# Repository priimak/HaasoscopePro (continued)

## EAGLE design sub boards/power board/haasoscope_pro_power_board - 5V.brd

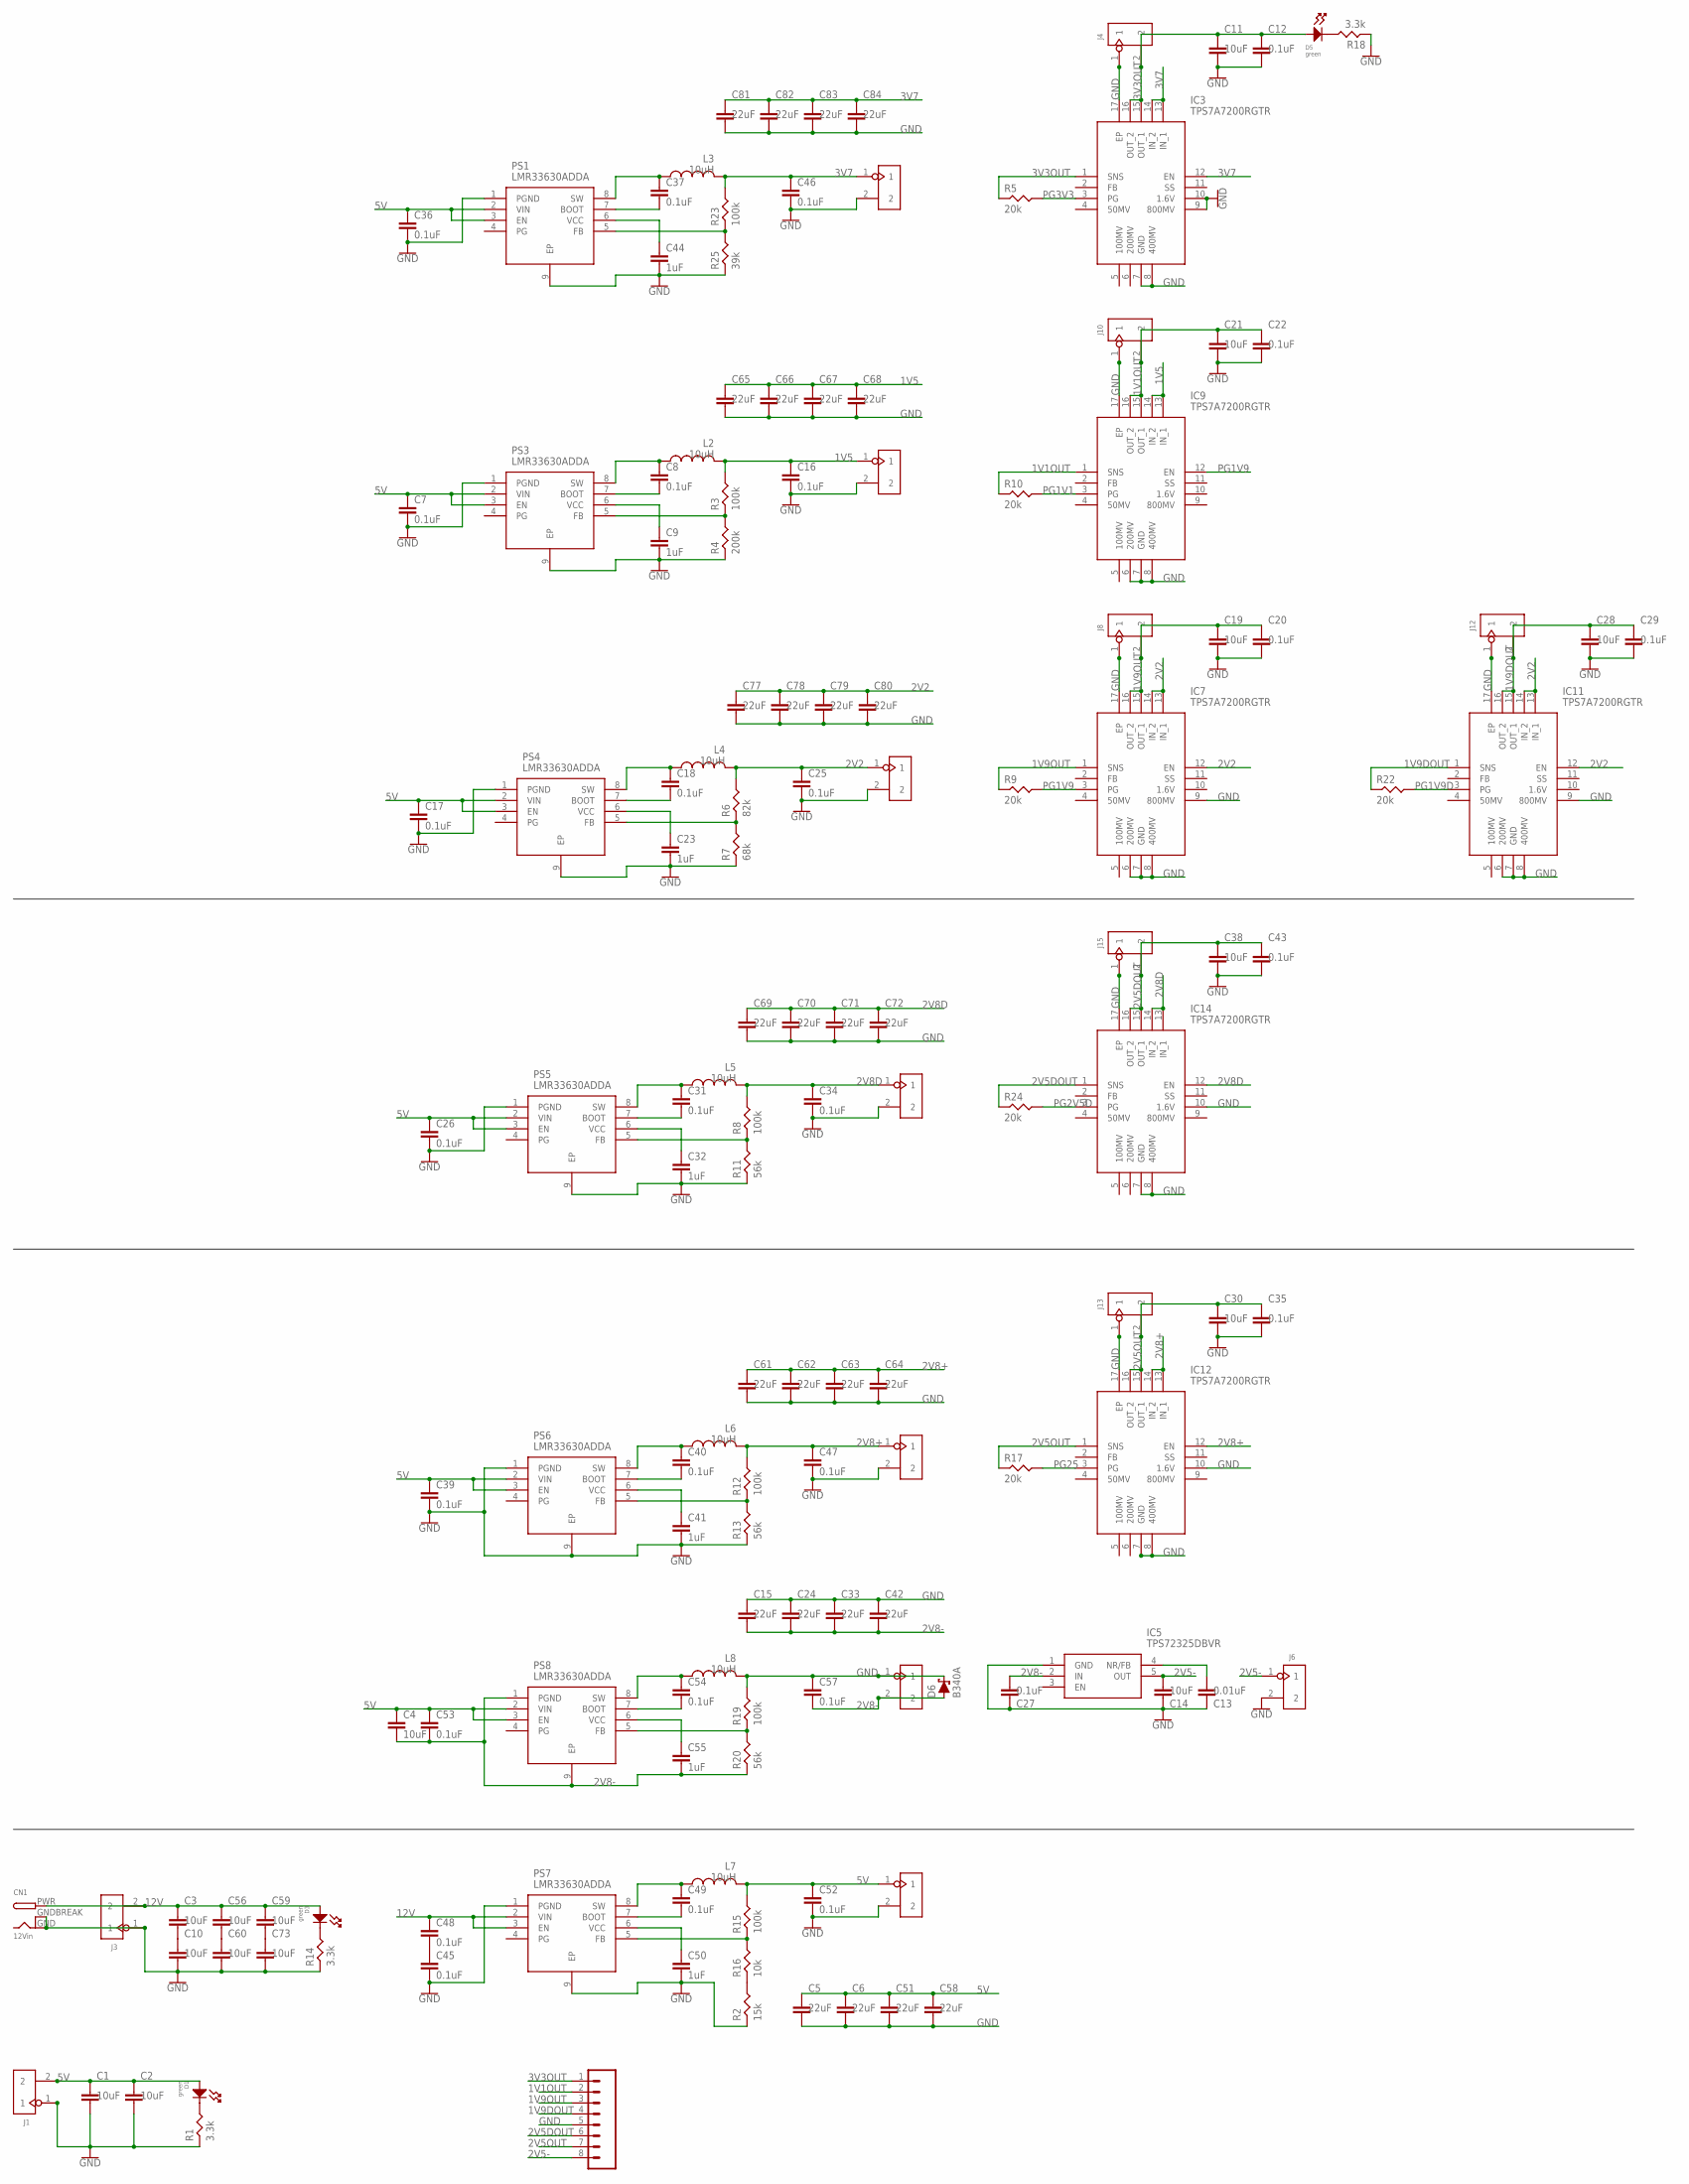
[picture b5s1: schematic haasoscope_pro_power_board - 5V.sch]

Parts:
C1, C2, C3, C4, C10, C11, C14, C19, C21, C28, C30, C38, C56, C59, C60, C73: 10uF; RESC0805_N
C5, C6, C15, C24, C33, C42, C51, C58, C61, C62, C63, C64, C65, C66, C67, C68, C69, C70, C71, C72, C77, C78, C79, C80, C81, C82, C83, C84: 22uF; RESC0805_N
C7, C8, C12, C16, C17, C18, C20, C22, C25, C26, C27, C29, C31, C34, C35, C36, C37, C39, C40, C43, C46, C47, C49, C52, C53, C54, C57: 0.1uF; RESC0402_N
C9, C23, C32, C41, C44, C50, C55: 1uF; RESC0402_N
C13: 0.01uF; RESC0402_N
C45, C48: 0.1uF; RESC0402_N; LCSC C307331
CN1: 12Vin; DCJACK_2MM_PTH
D1, D3, D5: green; LED0805
D6: B340A; SMA-DIODE; LCSC C64982
IC3, IC7, IC9, IC11, IC12, IC14: TPS7A7200RGTR; QFN50P300X300X100-17N
IC5: TPS72325DBVR; SOT95P280X145-5N
J1, J2, J3, J4, J5, J6, J7, J8, J9, J10, J11, J12, J13, J14, J15, J20: 2p-2.54; H2-2.54
J16: 8pin; 1X08
L2, L3, L4, L5, L6, L7, L8: 10uH; CDRH125; LCSC C339970
PS1, PS3, PS4, PS5, PS6, PS7, PS8: LMR33630ADDA; SOIC127P600X170-9N
R1, R14, R18: 3.3k; RES-0402
R2: 15k; RES-0402
R3, R8, R12, R15, R19, R23: 100k; RES-0402
R4: 200k; RES-0402
R5, R9, R10, R17, R22, R24: 20k; RES-0402
R6: 82k; RES-0402
R7: 68k; RES-0402
R11, R13, R20: 56k; RES-0402
R16: 10k; RES-0402
R25: 39k; RES-0402

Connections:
1V1OUT: C21.1, C22.1, IC9.1 (SNS), IC9.15 (OUT_1), IC9.16 (OUT_2), J10.2, J16.2, R10.P$1
1V5: C16.1, C65.1, C66.1, C67.1, C68.1, IC9.13 (IN_1), IC9.14 (IN_2), J2.1, L2.2, R3.P$2
1V9DOUT: C28.1, C29.1, IC11.1 (SNS), IC11.15 (OUT_1), IC11.16 (OUT_2), J12.2, J16.4, R22.P$1
1V9OUT: C19.1, C20.1, IC7.1 (SNS), IC7.15 (OUT_1), IC7.16 (OUT_2), J8.2, J16.3, R9.P$1
2V2: C25.1, C77.1, C78.1, C79.1, C80.1, IC7.12 (EN), IC7.13 (IN_1), IC7.14 (IN_2), IC11.12 (EN), IC11.13 (IN_1), IC11.14 (IN_2), J5.1, L4.2, R6.P$2
2V5-: C14.1, IC5.5 (OUT), J6.1, J16.8
2V5DOUT: C38.1, C43.1, IC14.1 (SNS), IC14.15 (OUT_1), IC14.16 (OUT_2), J15.2, J16.6, R24.P$1
2V5OUT: C30.1, C35.1, IC12.1 (SNS), IC12.15 (OUT_1), IC12.16 (OUT_2), J13.2, J16.7, R17.P$1
2V8+: C47.1, C61.1, C62.1, C63.1, C64.1, IC12.12 (EN), IC12.13 (IN_1), IC12.14 (IN_2), J9.1, L6.2, R12.P$2
2V8-: C4.2, C15.2, C24.2, C27.1, C33.2, C42.2, C53.2, C55.2, C57.2, D6.A, IC5.2 (IN), J20.2, PS8.1 (PGND), PS8.9 (EP), R20.P$1
2V8D: C34.1, C69.1, C70.1, C71.1, C72.1, IC14.12 (EN), IC14.13 (IN_1), IC14.14 (IN_2), J7.1, L5.2, R8.P$2
3V3OUT: C11.1, C12.1, D5.ANODE, IC3.1 (SNS), IC3.15 (OUT_1), IC3.16 (OUT_2), J4.2, J16.1, R5.P$1
3V7: C46.1, C81.1, C82.1, C83.1, C84.1, IC3.12 (EN), IC3.13 (IN_1), IC3.14 (IN_2), J14.1, L3.2, R23.P$2
5V: C1.1, C2.1, C4.1, C5.1, C6.1, C7.1, C17.1, C26.1, C36.1, C39.1, C51.1, C52.1, C53.1, C58.1, D1.ANODE, J1.2, J11.1, L7.2, PS1.2 (VIN), PS1.3 (EN), PS3.2 (VIN), PS3.3 (EN), PS4.2 (VIN), PS4.3 (EN), PS5.2 (VIN), PS5.3 (EN), PS6.2 (VIN), PS6.3 (EN), PS8.2 (VIN), PS8.3 (EN), R15.P$2
12V: C3.1, C48.1, C56.1, C59.1, CN1.PWR, D3.ANODE, J3.2, PS7.2 (VIN), PS7.3 (EN)
GND: C1.2, C2.2, C5.2, C6.2, C7.2, C9.2, C10.2, C11.2, C12.2, C13.2, C14.2, C15.1, C16.2, C17.2, C19.2, C20.2, C21.2, C22.2, C23.2, C24.1, C25.2, C26.2, C27.2, C28.2, C29.2, C30.2, C32.2, C33.1, C34.2, C35.2, C36.2, C38.2, C39.2, C41.2, C42.1, C43.2, C44.2, C45.2, C46.2, C47.2, C50.2, C51.2, C52.2, C57.1, C58.2, C60.2, C61.2, C62.2, C63.2, C64.2, C65.2, C66.2, C67.2, C68.2, C69.2, C70.2, C71.2, C72.2, C73.2, C77.2, C78.2, C79.2, C80.2, C81.2, C82.2, C83.2, C84.2, CN1.GND, CN1.GNDBREAK, D6.C, IC3.7 (GND), IC3.8 (400MV), IC3.9 (800MV), IC3.10 (1.6V), IC3.17 (EP), IC5.1 (GND), IC7.6 (200MV), IC7.7 (GND), IC7.8 (400MV), IC7.9 (800MV), IC7.17 (EP), IC9.6 (200MV), IC9.7 (GND), IC9.8 (400MV), IC9.17 (EP), IC11.6 (200MV), IC11.7 (GND), IC11.8 (400MV), IC11.9 (800MV), IC11.17 (EP), IC12.7 (GND), IC12.8 (400MV), IC12.10 (1.6V), IC12.17 (EP), IC14.7 (GND), IC14.8 (400MV), IC14.10 (1.6V), IC14.17 (EP), J1.1, J2.2, J3.1, J4.1, J5.2, J6.2, J7.2, J8.1, J9.2, J10.1, J11.2, J12.1, J13.1, J14.2, J15.1, J16.5, J20.1, L8.2, PS1.1 (PGND), PS1.9 (EP), PS3.1 (PGND), PS3.9 (EP), PS4.1 (PGND), PS4.9 (EP), PS5.1 (PGND), PS5.9 (EP), PS6.1 (PGND), PS6.9 (EP), PS7.1 (PGND), PS7.9 (EP), R1.P$1, R2.P$1, R4.P$1, R7.P$1, R11.P$1, R13.P$1, R14.P$1, R18.P$1, R19.P$2, R25.P$1
unnamed: C44.1, PS1.6 (VCC)
unnamed: C45.1, C48.2
unnamed: C3.2, C10.1
unnamed: C13.1, IC5.4 (NR/FB)
unnamed: D3.CATHODE, R14.P$2
unnamed: D5.CATHODE, R18.P$2
unnamed: D1.CATHODE, R1.P$2
unnamed: C37.1, L3.1, PS1.8 (SW)
unnamed: C37.2, PS1.7 (BOOT)
unnamed: PS1.5 (FB), R23.P$1, R25.P$2
unnamed: R2.P$2, R16.P$1
unnamed: C56.2, C60.1
unnamed: C8.1, L2.1, PS3.8 (SW)
unnamed: C8.2, PS3.7 (BOOT)
unnamed: PS3.5 (FB), R3.P$1, R4.P$2
unnamed: C9.1, PS3.6 (VCC)
unnamed: C18.1, L4.1, PS4.8 (SW)
unnamed: C18.2, PS4.7 (BOOT)
unnamed: PS4.5 (FB), R6.P$1, R7.P$2
unnamed: C23.1, PS4.6 (VCC)
unnamed: C31.1, L5.1, PS5.8 (SW)
unnamed: C31.2, PS5.7 (BOOT)
unnamed: PS5.5 (FB), R8.P$1, R11.P$2
unnamed: C32.1, PS5.6 (VCC)
unnamed: C40.1, L6.1, PS6.8 (SW)
unnamed: C40.2, PS6.7 (BOOT)
unnamed: PS6.5 (FB), R12.P$1, R13.P$2
unnamed: C41.1, PS6.6 (VCC)
unnamed: C49.1, L7.1, PS7.8 (SW)
unnamed: C49.2, PS7.7 (BOOT)
unnamed: PS7.5 (FB), R15.P$1, R16.P$2
unnamed: C50.1, PS7.6 (VCC)
unnamed: C54.1, L8.1, PS8.8 (SW)
unnamed: C54.2, PS8.7 (BOOT)
unnamed: PS8.5 (FB), R19.P$1, R20.P$2
unnamed: C55.1, PS8.6 (VCC)
unnamed: C59.2, C73.1
PG1V1: IC9.3 (PG), R10.P$2
PG1V9: IC7.3 (PG), IC9.12 (EN), R9.P$2
PG1V9D: IC11.3 (PG), R22.P$2
PG2V5D: IC14.3 (PG), R24.P$2
PG3V3: IC3.3 (PG), R5.P$2
PG25: IC12.3 (PG), R17.P$2

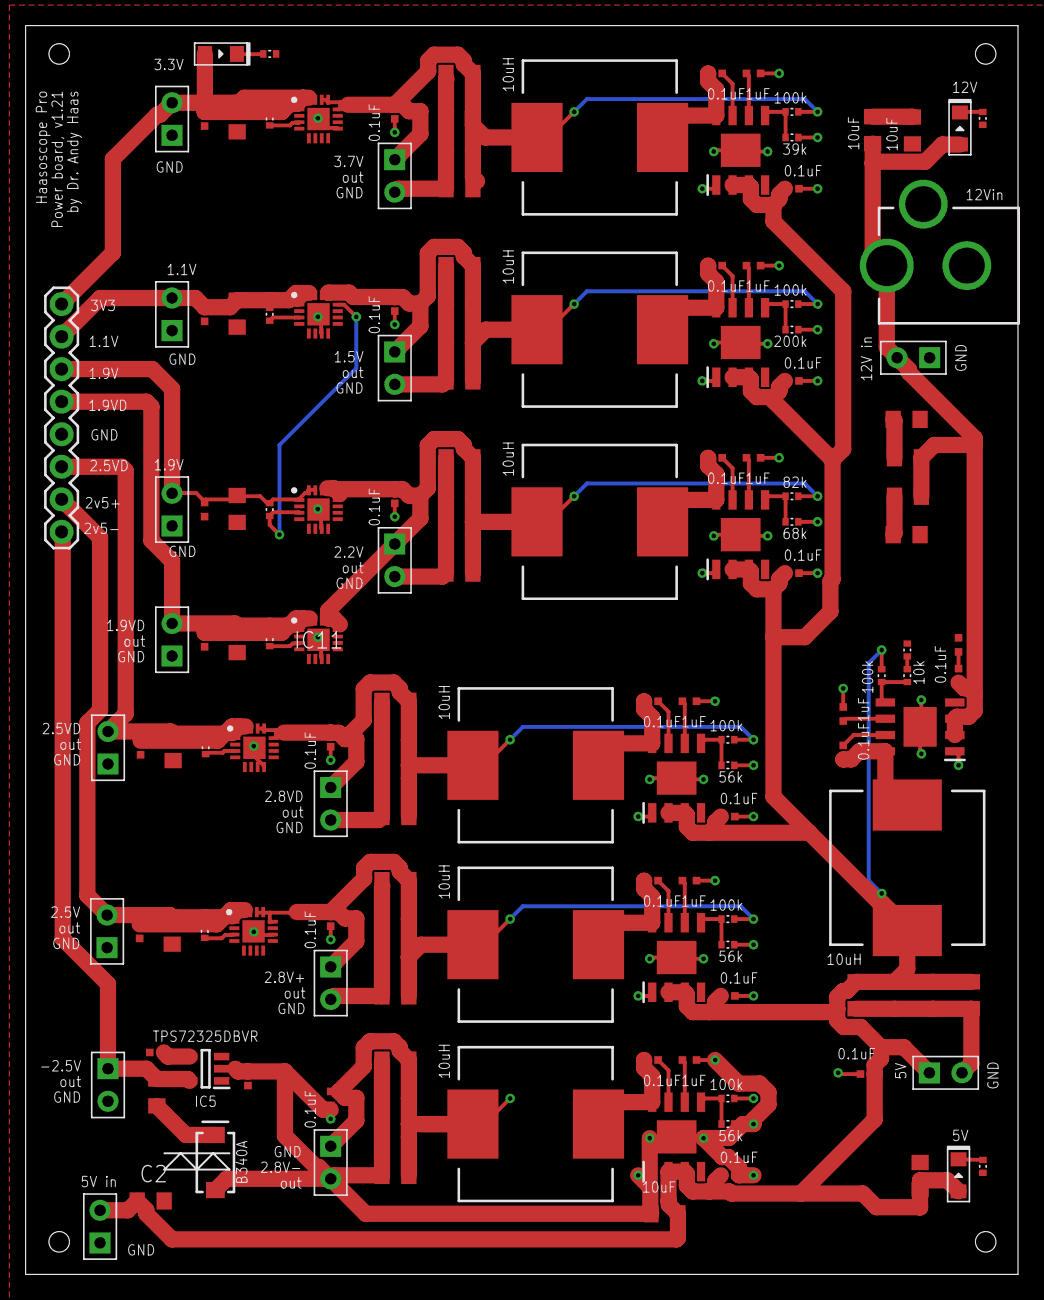
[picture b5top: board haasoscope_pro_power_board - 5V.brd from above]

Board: 2 copper layers, 77.5 x 97.5 mm, 148 parts (0 on the bottom side), 59 nets.

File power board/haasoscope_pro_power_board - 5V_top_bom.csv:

Comment,Designator,Footprint,LCSC Part #
0.1uF,C7 C8 C12 C16 C17 C18 C20 C22 C25 C26 C27 C29 C31 C34 C35 C36 C37 C39 C40 C43 C45 C46 C47 C48 C49 C52 C53 C54 C57,RESC0402_N,
0.01uF,C13,RESC0402_N,
1uF,C9 C23 C32 C41 C44 C50 C55,RESC0402_N,
3.3k,R1 R14 R18,RES-0402,
10k,R16,RES-0402,
10uF,C1 C2 C3 C4 C10 C11 C14 C19 C21 C28 C30 C38,RESC0805_N,
10uH,L2 L3 L4 L5 L6 L7 L8,CDRH125,C339970
15k,R2,RES-0402,
20k,R5 R9 R10 R17 R22 R24,RES-0402,
22uF,C5 C6 C15 C24 C33 C42 C51 C58 C61 C62 C63 C64 C65 C66 C67 C68 C69 C70 C71 C72 C77 C78 C79 C80 C81 C82 C83 C84,RESC0805_N,
39k,R25,RES-0402,
56k,R11 R13 R20,RES-0402,
68k,R7,RES-0402,
100k,R3 R6 R8 R12 R15 R19 R23,RES-0402,
200k,R4,RES-0402,
B340A,D6,SMA-DIODE,C64982
LMR33630ADDA,PS1 PS3 PS4 PS5 PS6 PS7 PS8,SOIC127P600X170-9N,
TPS7A7200RGTR,IC3 IC7 IC9 IC11 IC12 IC14,QFN50P300X300X100-17N,
TPS72325DBVR,IC5,SOT95P280X145-5N,
green,D1 D3 D5,LED0805,

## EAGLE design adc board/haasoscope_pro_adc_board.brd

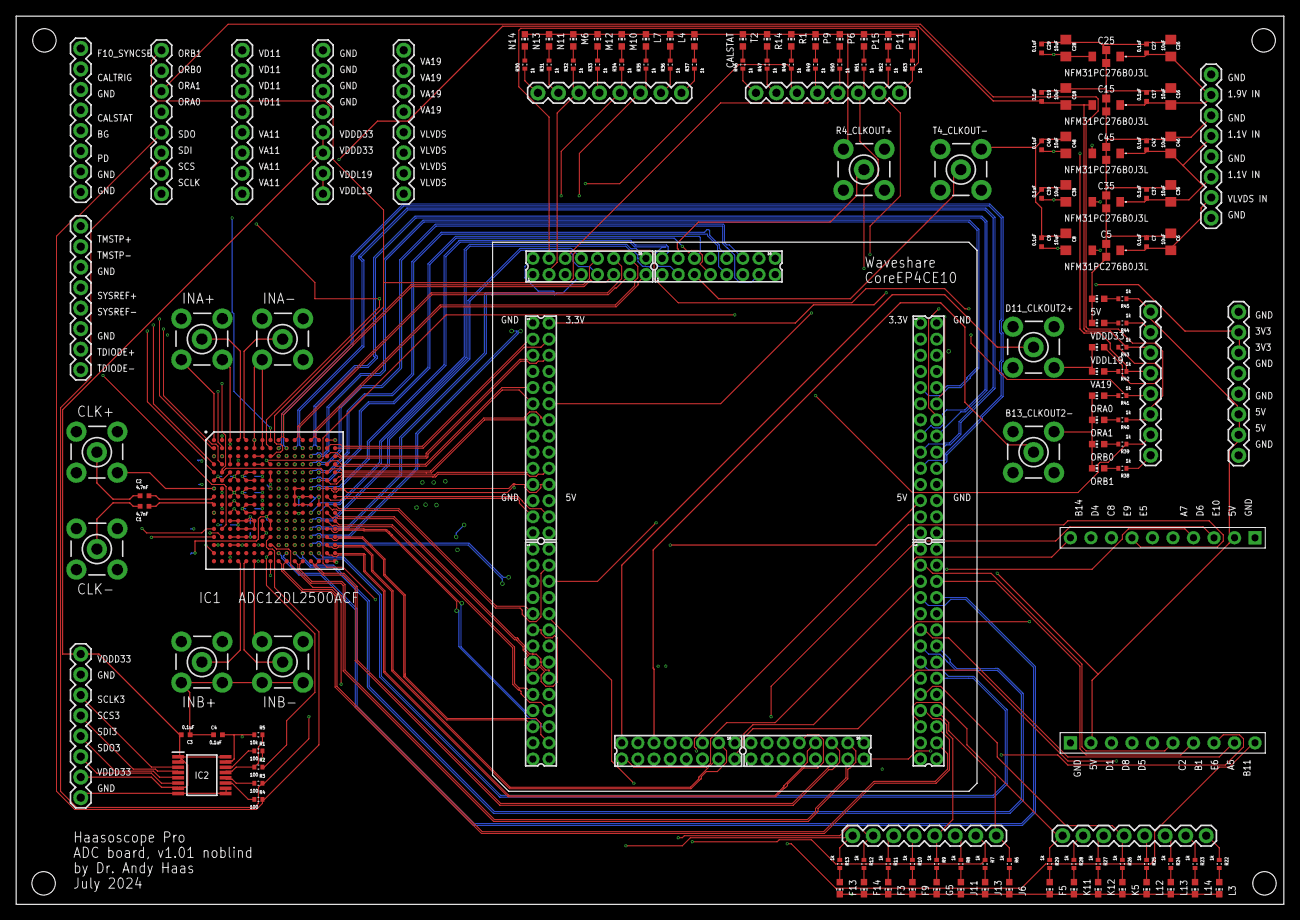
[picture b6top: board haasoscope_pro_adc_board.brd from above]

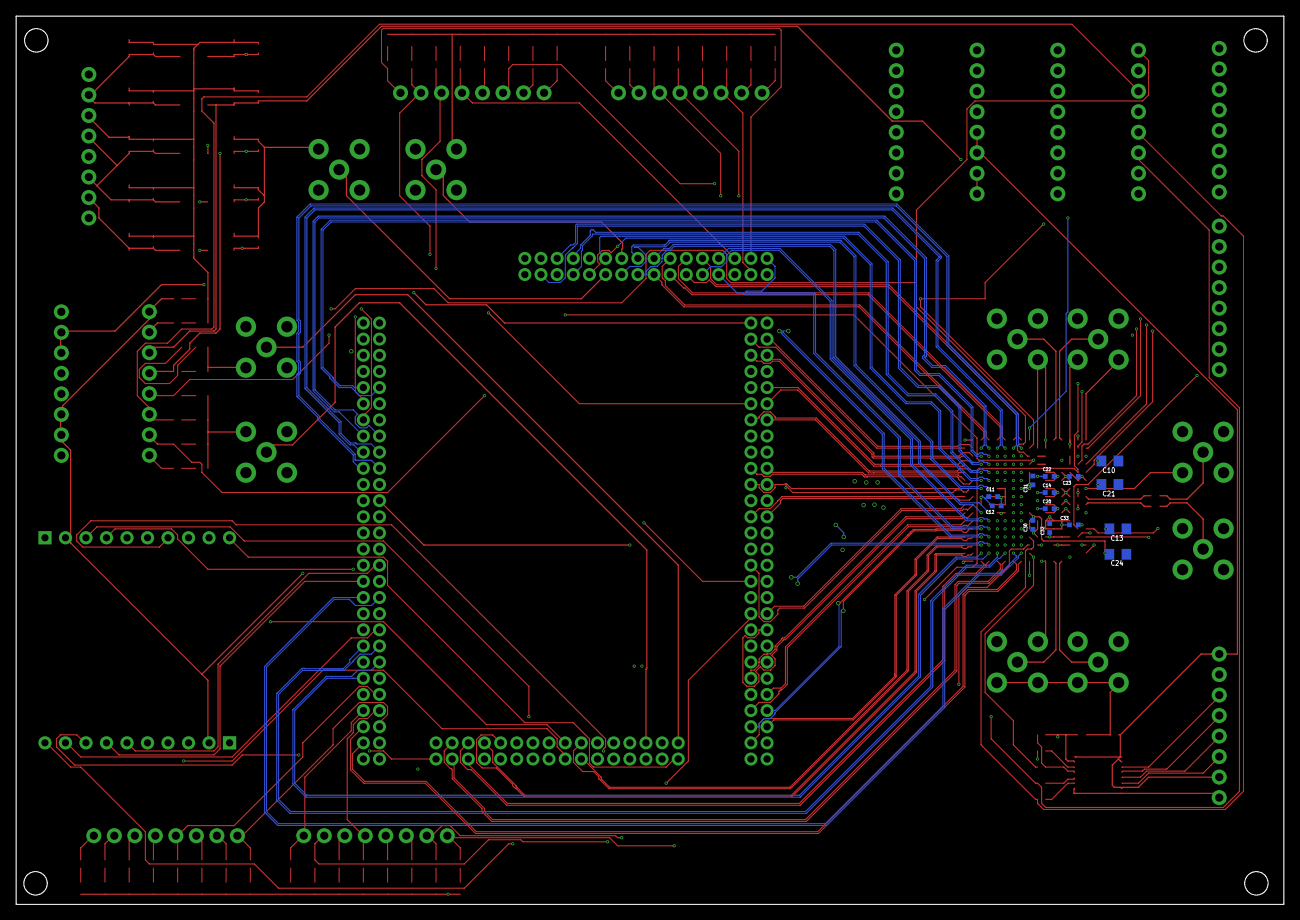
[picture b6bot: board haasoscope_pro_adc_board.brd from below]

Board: 10 copper layers, 157.0 x 110.0 mm, 164 parts (14 on the bottom side), 250 nets.

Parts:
B13_CLKOUT2-: BU-SMB-V
C1, C2: 4.7nF; RESC0402_N
C3, C4, C7, C9, C12, C17, C19, C20, C23, C27, C29, C31, C33, C37, C39, C47, C49: 0.1uF; RESC0402_N
C5, C15, C25, C35, C45: NFM31PC276B0J3L; NFM31HK103R1H3L
C6, C8, C10, C13, C16, C18, C21, C24, C26, C28, C36, C38, C46, C48: 10uF; RESC0805_N
C11, C14, C22, C30, C32: 1uF; RESC0402_N
CLK+: BU-SMB-V
CLK-: BU-SMB-V
D11_CLKOUT2+: BU-SMB-V
IC1: ADC12DL2500ACF; BGA256C100P16X16_1700X1700X331
IC2: SN74AVC4T774PWR; SOP65P640X120-16N
INA+: BU-SMB-V
INA-: BU-SMB-V
INB+: BU-SMB-V
INB-: BU-SMB-V
J1, J2, J3, J4, J5, J6, J7, J8, J10, J11, J12, J13, J16, J17: 8pin; 1X08
LED1, LED2, LED3, LED4, LED5, LED6, LED7, LED8, LED17, LED18, LED19, LED20, LED21, LED22, LED23, LED24, LED25, LED26, LED27, LED28, LED29, LED30, LED31, LED32, LED33, LED34, LED35, LED36, LED37, LED38, LED39, LED40, LED41, LED42, LED43, LED44, LED45, LED46, LED47, LED48: red; CHIP-LED0603
PINOUT1, PINOUT2: YELLOW-10P-2.54; H10-2.54
R1, R2, R3, R4: 100; RES-0402
R4_CLKOUT+: BU-SMB-V
R5: 10k; RES-0402
R6, R7, R8, R9, R10, R11, R12, R13, R22, R23, R24, R25, R26, R27, R28, R29, R30, R31, R32, R33, R34, R35, R36, R37, R38, R39, R40, R41, R42, R43, R44, R45, R46, R47, R48, R49, R50, R51, R52, R53: 1k; RES-0402
T4_CLKOUT-: BU-SMB-V
X1, X2, X15, X16: 87758-1616
X13, X14, X17, X18: 87758-2816

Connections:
3V3: J6.6, J6.7, X13.1, X18.2
5V: J6.2, J6.3, J12.1, PINOUT1.2, PINOUT2.2, R45.P$1, X13.23, X18.24
A5: PINOUT1.9, X14.11
A7: PINOUT2.5, X2.15
B1: PINOUT1.7, X14.6
B11: PINOUT1.10, X1.11
B13_CLKOUT2N: B13_CLKOUT2-.1, X1.6
B14: PINOUT2.10, X1.1
BG: IC1.D2, J17.5
C2: PINOUT1.6, X14.3
C8: PINOUT2.8, X1.16
CALSTAT: IC1.B1, J13.8, J17.4, R46.P$1
CALTRIG: IC1.B2, J17.2
CLK_AC_N: C1.1, IC1.J1
CLK_AC_P: C2.2, IC1.H1
CLK_N: C1.2, CLK-.1
CLK_P: C2.1, CLK+.1
D1: PINOUT1.3, X14.4
D4: PINOUT2.9, X14.17
D5: PINOUT1.5, X2.9
D6: PINOUT2.4, X2.7
D8: PINOUT1.4, X1.15
D11_CLKOUT2P: D11_CLKOUT2+.1, X1.2
DIFF1_N: IC1.M10, X14.1
DIFF1_P: IC1.M9, X14.2
DIFF2_N: IC1.L10, X13.27
DIFF2_P: IC1.L9, X13.28
DIFF3_N: IC1.K10, X13.25
DIFF3_P: IC1.K9, X13.26
DIFF4_N: IC1.C12, X13.4
DIFF4_P: IC1.C11, X14.20
DIFF5_N: IC1.J10, X13.21
DIFF5_P: IC1.J9, X13.22
DIFF6_N: IC1.B10, X13.19
DIFF6_P: IC1.B9, X13.20
DIFF7_N: IC1.B12, X13.17
DIFF7_P: IC1.B11, X13.18
DIFF8_N: IC1.B14, X13.15
DIFF8_P: IC1.B13, X13.16
DIFF9_N: IC1.C14, X13.10
DIFF9_P: IC1.C13, X13.9
DIFF10_N: IC1.F14, X15.7
DIFF10_P: IC1.F13, X15.6
DIFF11_N: IC1.C10, X13.8
DIFF11_P: IC1.C9, X13.7
DIFF12_N: IC1.E10, X15.11
DIFF12_P: IC1.E9, X15.14
DIFF13_N: IC1.G14, X15.3
DIFF13_P: IC1.G13, X15.2
DIFF14_N: IC1.K14, X15.1
DIFF14_P: IC1.K13, X16.16
DIFF15_N: IC1.A14, X16.15
DIFF15_P: IC1.A13, X16.14
DIFF16_N: IC1.D14, X15.13
DIFF16_P: IC1.D13, X15.12
DIFF17_N: IC1.D10, X13.6
DIFF17_P: IC1.D9, X13.3
DIFF18_N: IC1.A12, X16.13
DIFF18_P: IC1.A11, X16.12
DIFF19_N: IC1.A10, X16.11
DIFF19_P: IC1.A9, X16.10
DIFF20_N: IC1.E14, X15.9
DIFF20_P: IC1.E13, X15.10
DIFF21_N: IC1.F10, X16.5
DIFF21_P: IC1.F9, X15.8
DIFF22_N: IC1.L14, X16.9
DIFF22_P: IC1.L13, X16.8
DIFF23_N: IC1.M14, X16.7
DIFF23_P: IC1.M13, X16.2
DIFF24_N: IC1.B16, X18.4
DIFF24_P: IC1.B15, X18.3
DIFF25_N: IC1.P14, X18.28
DIFF25_P: IC1.P13, X17.16
DIFF26_N: IC1.C16, X18.6
DIFF26_P: IC1.C15, X18.5
DIFF27_N: IC1.D12, X18.10
DIFF27_P: IC1.D11, X18.8
DIFF28_N: IC1.J16, X17.9
DIFF28_P: IC1.J15, X17.4
DIFF29_N: IC1.N14, X16.1
DIFF29_P: IC1.N13, X17.2
DIFF30_N: IC1.D16, X18.11
DIFF30_P: IC1.D15, X18.9
DIFF31_N: IC1.E16, X18.13
DIFF31_P: IC1.E15, X18.14
DIFF32_N: IC1.G10, X18.15
DIFF32_P: IC1.G9, X18.16
DIFF33_N: IC1.H10, X18.17
DIFF33_P: IC1.H9, X18.18
DIFF34_N: IC1.F16, X18.19
DIFF34_P: IC1.F15, X18.20
DIFF35_N: IC1.K16, X17.18
DIFF35_P: IC1.K15, X17.11
DIFF36_N: IC1.G16, X18.22
DIFF36_P: IC1.G15, X18.21
DIFF37_N: IC1.H16, X18.26
DIFF37_P: IC1.H15, X18.25
DIFF38_N: IC1.L16, X17.19
DIFF38_P: IC1.L15, X17.22
DIFF39_N: IC1.M16, X17.21
DIFF39_P: IC1.M15, X17.24
DIFF40_N: IC1.N16, X17.26
DIFF40_P: IC1.N15, X17.23
DIFF41_N: IC1.P12, X1.8
DIFF41_P: IC1.P11, X1.5
DIFF42_N: IC1.N12, X1.10
DIFF42_P: IC1.N11, X1.7
DIFF43_N: IC1.M12, X1.9
DIFF43_P: IC1.M11, X1.12
DIFF44_N: IC1.F12, X1.3
DIFF44_P: IC1.F11, X2.3
DIFF45_N: IC1.E12, X17.15
DIFF45_P: IC1.E11, X17.25
DIFF46_N: IC1.P16, X1.13
DIFF46_P: IC1.P15, X1.14
DIFF47_N: IC1.T14, X2.11
DIFF47_P: IC1.T13, X2.12
DIFF48_N: IC1.T12, X2.13
DIFF48_P: IC1.T11, X2.14
DIFF49_N: IC1.L12, X2.6
DIFF49_P: IC1.L11, X2.5
DIFF50_N: IC1.T10, X14.26
DIFF50_P: IC1.T9, X14.24
DIFF51_N: IC1.R12, X14.13
DIFF51_P: IC1.R11, X14.14
DIFF52_N: IC1.P10, X14.5
DIFF52_P: IC1.P9, X14.12
DIFF53_N: IC1.N10, X14.9
DIFF53_P: IC1.N9, X14.10
DIFF54_N: IC1.R16, X2.10
DIFF54_P: IC1.R15, X2.8
DIFF55_N: IC1.R10, X14.7
DIFF55_P: IC1.R9, X14.8
DIFF56_N: IC1.R14, X14.18
DIFF56_P: IC1.R13, X14.15
E5: PINOUT2.6, X14.25
E6: PINOUT1.8, X2.16
E9: PINOUT2.7, X2.1
E10: PINOUT2.3, X2.2
F3: J8.3, R11.P$1, X14.16
F5: J10.1, R29.P$1, X14.23
F9: J8.4, R10.P$1, X2.4
F10_SYNCSE: IC1.E2, J17.1, X1.4
F13: J8.1, R13.P$1, X17.17
F14: J8.2, R12.P$1, X17.20
G5: J8.5, R9.P$1, X14.21
GND: B13_CLKOUT2-.2, B13_CLKOUT2-.3, B13_CLKOUT2-.4, B13_CLKOUT2-.5, C3.1, C4.1, C5.2, C5.4, C6.1, C7.1, C8.1, C9.1, C10.1, C11.1, C12.1, C13.1, C14.1, C15.2, C15.4, C16.1, C17.1, C18.1, C19.1, C20.1, C21.1, C22.1, C23.1, C24.1, C25.2, C25.4, C26.1, C27.1, C28.1, C29.1, C30.1, C31.1, C32.1, C33.1, C35.2, C35.4, C36.1, C37.1, C38.1, C39.1, C45.2, C45.4, C46.1, C47.1, C48.1, C49.1, CLK+.2, CLK+.3, CLK+.4, CLK+.5, CLK-.2, CLK-.3, CLK-.4, CLK-.5, D11_CLKOUT2+.2, D11_CLKOUT2+.3, D11_CLKOUT2+.4, D11_CLKOUT2+.5, IC1.A1, IC1.A2, IC1.A3, IC1.A6, IC1.A7, IC1.A15, IC1.A16, IC1.B3, IC1.B4, IC1.B5, IC1.B6, IC1.B7, IC1.C1, IC1.C2, IC1.C3, IC1.C4, IC1.C5, IC1.C6, IC1.C7, IC1.D3, IC1.D4, IC1.D5, IC1.D6, IC1.D7, IC1.E3, IC1.E7, IC1.F1, IC1.F2, IC1.F7, IC1.G1, IC1.G2, IC1.G7, IC1.H2, IC1.H7, IC1.H8, IC1.H14, IC1.J2, IC1.J7, IC1.J8, IC1.J14, IC1.K1, IC1.K2, IC1.K7, IC1.L1, IC1.L2, IC1.L7, IC1.M3, IC1.M7, IC1.N3, IC1.N4, IC1.N5, IC1.N6, IC1.N7, IC1.P1, IC1.P2, IC1.P3, IC1.P4, IC1.P5, IC1.P6, IC1.P7, IC1.R2, IC1.R3, IC1.R4, IC1.R5, IC1.R6, IC1.R7, IC1.T1, IC1.T2, IC1.T3, IC1.T6, IC1.T7, IC1.T15, IC1.T16, IC2.8, IC2.9, IC2.10, INA+.2, INA+.3, INA+.4, INA+.5, INA-.2, INA-.3, INA-.4, INA-.5, INB+.2, INB+.3, INB+.4, INB+.5, INB-.2, INB-.3, INB-.4, INB-.5, J2.5, J2.6, J2.7, J2.8, J4.2, J4.8, J5.1, J5.4, J5.6, J5.8, J6.1, J6.4, J6.5, J6.8, J7.3, J7.6, J17.3, J17.7, J17.8, LED1.C, LED2.C, LED3.C, LED4.C, LED5.C, LED6.C, LED7.C, LED8.C, LED17.C, LED18.C, LED19.C, LED20.C, LED21.C, LED22.C, LED23.C, LED24.C, LED25.C, LED26.C, LED27.C, LED28.C, LED29.C, LED30.C, LED31.C, LED32.C, LED33.C, LED34.C, LED35.C, LED36.C, LED37.C, LED38.C, LED39.C, LED40.C, LED41.C, LED42.C, LED43.C, LED44.C, LED45.C, LED46.C, LED47.C, LED48.C, PINOUT1.1, PINOUT2.1, R4_CLKOUT+.2, R4_CLKOUT+.3, R4_CLKOUT+.4, R4_CLKOUT+.5, T4_CLKOUT-.2, T4_CLKOUT-.3, T4_CLKOUT-.4, T4_CLKOUT-.5, X13.2, X13.24, X18.1, X18.23
INA_N: IC1.A5, INA-.1
INA_P: IC1.A4, INA+.1
INB_N: IC1.T5, INB-.1
INB_P: IC1.T4, INB+.1
J6: J8.8, R6.P$1, X14.22
J11: J8.6, R8.P$1, X17.13
J13: J8.7, R7.P$1, X17.10
K5: J10.4, R26.P$1, X14.19
K11: J10.2, R28.P$1, X17.14
K12: J10.3, R27.P$1, X17.12
L3: J10.8, R22.P$1, X13.11
L4: J11.1, R37.P$1, X13.12
L7: J11.2, R36.P$1, X15.15
L12: J10.5, R25.P$1, X17.8
L13: J10.6, R24.P$1, X17.6
L14: J10.7, R23.P$1, X17.7
M6: J11.5, R33.P$1, X15.16
M10: J11.3, R35.P$1, X18.27
M12: J11.4, R34.P$1, X17.5
N11: J11.6, R32.P$1, X16.3
N13: J11.7, R31.P$1, X17.1
N14: J11.8, R30.P$1, X17.3
unnamed: LED1.A, R13.P$2
unnamed: LED2.A, R12.P$2
unnamed: LED3.A, R11.P$2
unnamed: LED4.A, R10.P$2
unnamed: LED5.A, R9.P$2
unnamed: LED6.A, R8.P$2
unnamed: LED7.A, R7.P$2
unnamed: LED8.A, R6.P$2
unnamed: LED17.A, R29.P$2
unnamed: LED18.A, R28.P$2
unnamed: LED19.A, R27.P$2
unnamed: LED20.A, R26.P$2
unnamed: LED21.A, R25.P$2
unnamed: LED22.A, R24.P$2
unnamed: LED23.A, R23.P$2
unnamed: LED24.A, R22.P$2
unnamed: LED25.A, R37.P$2
unnamed: LED26.A, R36.P$2
unnamed: LED27.A, R35.P$2
unnamed: LED28.A, R34.P$2
unnamed: LED29.A, R33.P$2
unnamed: LED30.A, R32.P$2
unnamed: LED31.A, R31.P$2
unnamed: LED32.A, R30.P$2
unnamed: LED33.A, R45.P$2
unnamed: LED34.A, R44.P$2
unnamed: LED35.A, R43.P$2
unnamed: LED36.A, R42.P$2
unnamed: LED37.A, R41.P$2
unnamed: LED38.A, R40.P$2
unnamed: LED39.A, R39.P$2
unnamed: LED40.A, R38.P$2
unnamed: LED41.A, R53.P$2
unnamed: LED42.A, R52.P$2
unnamed: LED43.A, R51.P$2
unnamed: LED44.A, R50.P$2
unnamed: LED45.A, R49.P$2
unnamed: LED46.A, R48.P$2
unnamed: LED47.A, R47.P$2
unnamed: LED48.A, R46.P$2
ORA0: IC1.B8, J12.5, J16.5, R41.P$1
ORA1: IC1.A8, J12.6, J16.6, R40.P$1
ORB0: IC1.D8, J12.7, J16.7, R39.P$1
ORB1: IC1.C8, J12.8, J16.8, R38.P$1
P6: J13.3, R51.P$1, X13.5
P9: J13.4, R50.P$1, X16.6
P11: J13.1, R53.P$1, X16.4
P15: J13.2, R52.P$1, X18.12
PD: IC1.R1, J17.6
R1: J13.5, R49.P$1, X13.13
R4_CLKOUT1P: R4_CLKOUT+.1, X15.4
R14: J13.6, R48.P$1, X18.7
SCLK: IC1.T8, J16.1, R1.P$2
SCLK3: IC2.3, J4.3
SCLKT: IC2.14, R1.P$1
SCS: IC1.R8, J16.2, R2.P$2
SCS3: IC2.4, J4.4
SCST: IC2.13, R2.P$1, R5.P$2
SDI: IC1.P8, J16.3, R3.P$2
SDI3: IC2.5, J4.5
SDIT: IC2.12, R3.P$1
SDO: IC1.N8, J16.4, R4.P$2
SDO3: IC2.6, J4.6
SDOT: IC2.11, R4.P$1
SYSREF1: IC1.M1, J7.4
SYSREF2: IC1.N1, J7.5
T2: J13.7, R47.P$1, X13.14
T4_CLKOUT1N: T4_CLKOUT-.1, X15.5
TDIODE1: IC1.M2, J7.7
TDIODE2: IC1.N2, J7.8
TMSTP1: IC1.D1, J7.1
TMSTP2: IC1.E1, J7.2
V11_IN: C35.1, C36.2, C37.2, C45.1, C46.2, C47.2, J5.3, J5.5
V19_IN: C15.1, C16.2, C17.2, C25.1, C26.2, C27.2, J5.7
VA11: C21.2, C22.2, C23.2, C32.2, C33.2, C35.3, C38.2, C39.2, IC1.E4, IC1.E5, IC1.E6, IC1.F3, IC1.F4, IC1.F5, IC1.F6, IC1.L3, IC1.L4, IC1.L5, IC1.L6, IC1.M4, IC1.M5, IC1.M6, J3.1, J3.2, J3.3, J3.4
VA19: C13.2, C14.2, C20.2, C25.3, C28.2, C29.2, IC1.G3, IC1.G4, IC1.G5, IC1.G6, IC1.H3, IC1.H4, IC1.H5, IC1.H6, IC1.J3, IC1.J4, IC1.J5, IC1.J6, IC1.K3, IC1.K4, IC1.K5, IC1.K6, J1.5, J1.6, J1.7, J1.8, J12.4, R42.P$1
VD11: C24.2, C30.2, C31.2, C45.3, C48.2, C49.2, IC1.E8, IC1.F8, IC1.G8, IC1.K8, IC1.L8, IC1.M8, J3.5, J3.6, J3.7, J3.8
VDDD33: C3.2, IC2.1, IC2.2, IC2.7, IC2.16, J2.3, J2.4, J4.1, J4.7, J12.2, R44.P$1
VDDL19: C4.2, C15.3, C18.2, C19.2, IC2.15, J2.1, J2.2, J12.3, R5.P$1, R43.P$1
VLVDS: C5.3, C8.2, C9.2, C10.2, C11.2, C12.2, IC1.G11, IC1.G12, IC1.H11, IC1.H12, IC1.H13, IC1.J11, IC1.J12, IC1.J13, IC1.K11, IC1.K12, J1.1, J1.2, J1.3, J1.4
VLVDS_IN: C5.1, C6.2, C7.2, J5.2

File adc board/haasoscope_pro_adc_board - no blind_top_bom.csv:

Comment,Designator,Footprint,LCSC Part #
0.1uF,C3 C4 C7 C9 C17 C19 C27 C29 C37 C39 C47 C49,RESC0402_N,
1k,R6 R7 R8 R9 R10 R11 R12 R13 R22 R23 R24 R25 R26 R27 R28 R29 R30 R31 R32 R33 R34 R35 R36 R37 R38 R39 R40 R41 R42 R43 R44 R45 R46 R47 R48 R49 R50 R51 R52 R53,RES-0402,
4.7nF,C1 C2,RESC0402_N,
10k,R5,RES-0402,
10uF,C6 C8 C16 C18 C26 C28 C36 C38 C46 C48,RESC0805_N,
100,R1 R2 R3 R4,RES-0402,
ADC12DL2500ACF,IC1,BGA256C100P16X16_1700X1700X331,
NFM31PC276B0J3L,C5 C15 C25 C35 C45,NFM31HK103R1H3L,
SN74AVC4T774PWR,IC2,SOP65P640X120-16N,
red,LED1 LED2 LED3 LED4 LED5 LED6 LED7 LED8 LED17 LED18 LED19 LED20 LED21 LED22 LED23 LED24 LED25 LED26 LED27 LED28 LED29 LED30 LED31 LED32 LED33 LED34 LED35 LED36 LED37 LED38 LED39 LED40 LED41 LED42 LED43 LED44 LED45 LED46 LED47 LED48,CHIP-LED0603,
